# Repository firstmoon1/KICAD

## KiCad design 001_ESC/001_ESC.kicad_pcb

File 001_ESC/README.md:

THIS IS A DEMONSTRATION OF ESC(ELECTRONIC SPEED CONTROLLER) PROJECT,THAT WAS DONE BY MY INTEREST,GERBER AND PDF IS AVAILABLE.

PCB

3D FRONT OVERLAY

3D BACK OVERLAY

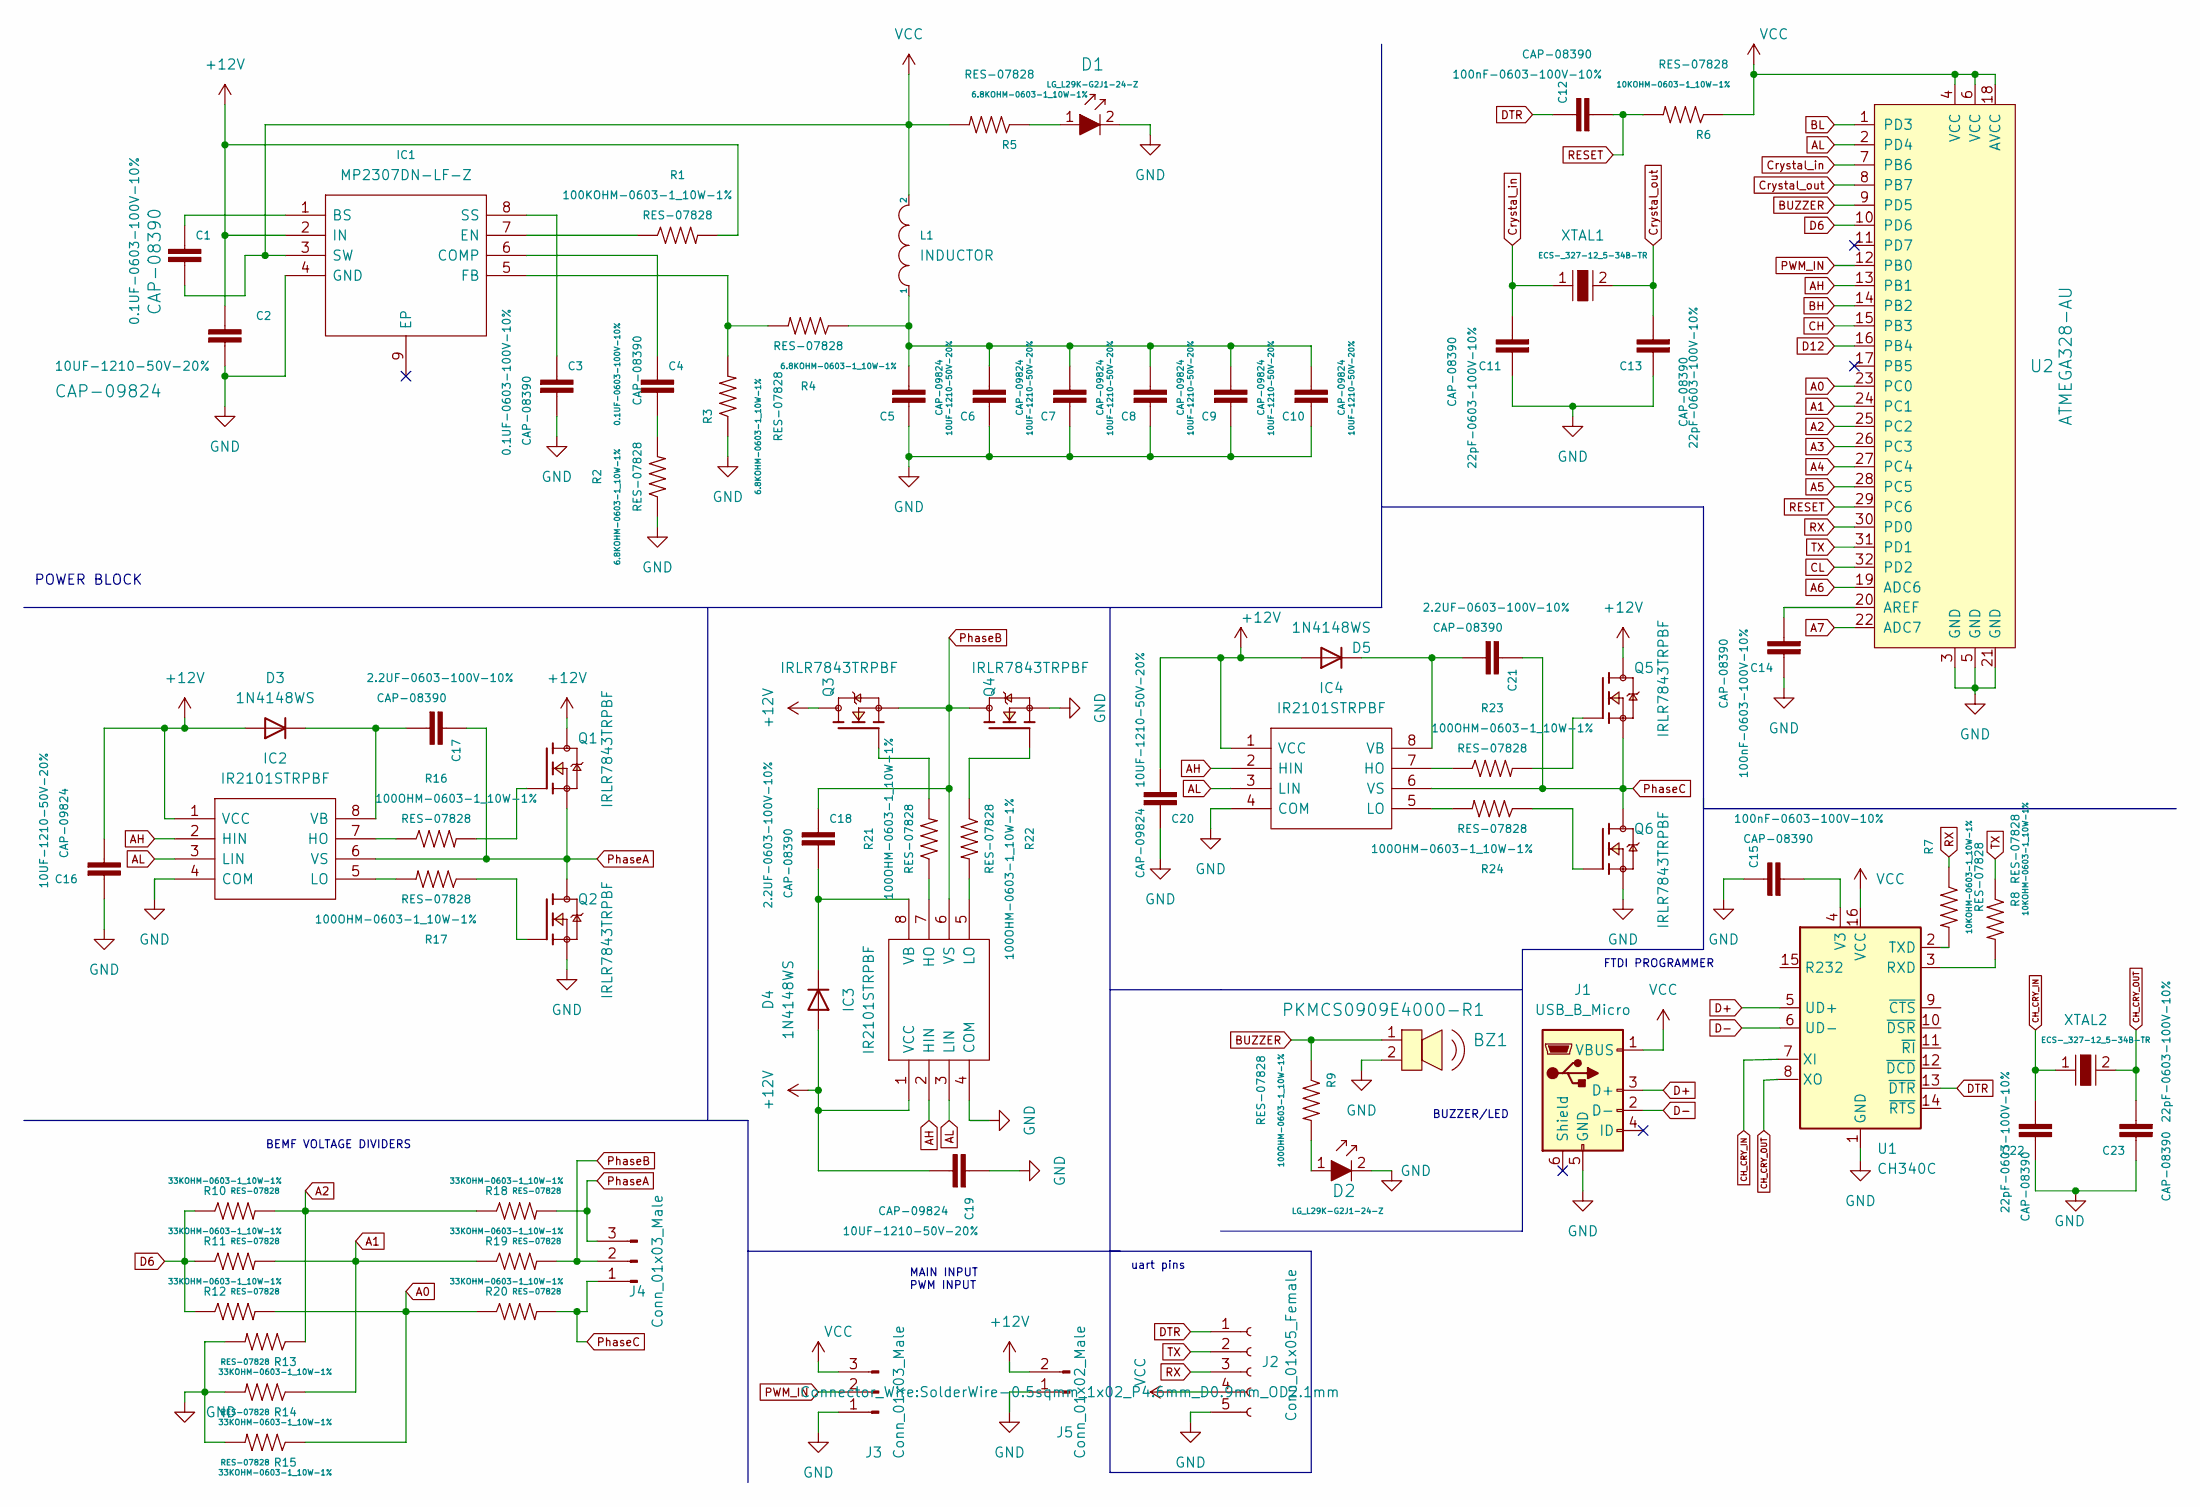
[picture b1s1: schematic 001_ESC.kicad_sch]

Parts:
BZ1: PKMCS0909E4000-R1; Buzzer_CUI_CPT-9019S-SMT; MPN PKMCS0909E4000-R1; Digi-Key_PN 490-9647-1-ND
C1, C3, C4: 0.1UF-0603-100V-10%; 0603
C2, C5, C6, C7, C8, C9, C10, C16, C19, C20: 10UF-1210-50V-20%; 1210
C11, C13, C22, C23: 22pF-0603-100V-10%; 0603
C12, C14, C15: 100nF-0603-100V-10%; 0603
C17, C18, C21: 2.2UF-0603-100V-10%; 0603
D1, D2: LG_L29K-G2J1-24-Z; 0603; MPN LG L29K-G2J1-24-Z; Digi-Key_PN 475-2709-1-ND
D3, D4, D5: 1N4148WS; D_SOD-323
IC1: MP2307DN-LF-Z; SOIC127P600X170-9N; Manufacturer_Part_Number MP2307DN-LF-Z; Mouser Part Number 946-MP2307DNLFZ
IC2, IC3, IC4: IR2101STRPBF; SOIC127P600X175-8N; Manufacturer_Part_Number IR2101STRPBF; Mouser Part Number 942-IR2101STRPBF
J1: USB_B_Micro; USB_Mini-B_Lumberg_2486_01_Horizontal
J2: Conn_01x05_Female; SolderWire-1.5sqmm_1x05_P6mm_D1.7mm_OD3mm
J3, J4: Conn_01x03_Male; SolderWire-0.5sqmm_1x03_P4.8mm_D0.9mm_OD2.3mm
J5: Conn_01x02_Male; SolderWire-0.5sqmm_1x02_P4.6mm_D0.9mm_OD2.1mm
L1: INDUCTOR; L_7.3x7.3_H4.5
Q1, Q2, Q3, Q4, Q5, Q6: IRLR7843TRPBF; TO229P990X239-3_4N; Digi-Key_Part_Number IRLR7843PBFTR-ND
R1: 100KOHM-0603-1_10W-1%; R_0201_0603Metric_Pad0.64x0.40mm_HandSolder
R2, R3, R4, R5: 6.8KOHM-0603-1_10W-1%; R_0201_0603Metric_Pad0.64x0.40mm_HandSolder
R6, R7, R8: 10KOHM-0603-1_10W-1%; R_0201_0603Metric_Pad0.64x0.40mm_HandSolder
R9, R16, R17, R21, R22, R23, R24: 100OHM-0603-1_10W-1%; R_0201_0603Metric_Pad0.64x0.40mm_HandSolder
R10, R11, R12, R13, R14, R15, R18, R19, R20: 33KOHM-0603-1_10W-1%; R_0201_0603Metric_Pad0.64x0.40mm_HandSolder
U1: CH340C; SOIC-16_3.9x9.9mm_P1.27mm
U2: ATMEGA328-AU; TQFP-32_7x7mm; MPN ATMEGA328-AU; Digi-Key_PN ATMEGA328-AU-ND
XTAL1, XTAL2: ECS-_327-12_5-34B-TR; SMD-2_3.2x1.5mm; MPN ECS-.327-12.5-34B-TR; Digi-Key_PN XC1617CT-ND

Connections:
+12V: C2.1, C16.1, C19.1, C20.1, D3.2 (A), D4.2 (A), D5.2 (A), IC1.2 (IN), IC2.1 (VCC), IC3.1 (VCC), IC4.1 (VCC), J5.2, Q1.4, Q3.4, Q5.4, R1.2
A0: R12.2, R15.1, R20.1, U2.23 (PC0)
A1: R11.2, R14.1, R19.1, U2.24 (PC1)
A2: R10.2, R13.1, R18.1, U2.25 (PC2)
A3: U2.26 (PC3)
A4: U2.27 (PC4)
A5: U2.28 (PC5)
A6: U2.19 (ADC6)
A7: U2.22 (ADC7)
AH: IC2.2 (HIN), IC3.2 (HIN), IC4.2 (HIN), U2.13 (PB1)
AL: IC2.3 (LIN), IC3.3 (LIN), IC4.3 (LIN), U2.2 (PD4)
BH: U2.14 (PB2)
BL: U2.1 (PD3)
BUZZER: BZ1.1, R9.1, U2.9 (PD5)
CH: U2.15 (PB3)
CH_CRY_IN: C22.2, U1.7 (XI), XTAL2.1
CH_CRY_OUT: C23.2, U1.8 (XO), XTAL2.2
CL: U2.32 (PD2)
Crystal_in: C11.2, U2.7 (PB6), XTAL1.1
Crystal_out: C13.2, U2.8 (PB7), XTAL1.2
D6: R10.1, R11.1, R12.1, U2.10 (PD6)
D12: U2.16 (PB4)
D+: J1.3 (D+), U1.5 (UD+)
D-: J1.2 (D-), U1.6 (UD-)
DTR: C12.1, J2.1, U1.13 (~DTR)
GND: BZ1.2, C2.2, C3.2, C5.2, C6.2, C7.2, C8.2, C9.2, C10.2, C11.1, C13.1, C14.1, C15.1, C16.2, C19.2, C20.2, C22.1, C23.1, D1.2, D2.2, IC1.4 (GND), IC2.4 (COM), IC3.4 (COM), IC4.4 (COM), J1.5 (GND), J2.5, J3.1, J5.1, Q2.3, Q4.3, Q6.3, R2.1, R3.1, R13.2, R14.2, R15.2, U1.1 (GND), U2.3 (GND), U2.5 (GND), U2.21 (GND)
unnamed: C1.1, IC1.1 (BS)
unnamed: C3.1, IC1.8 (SS)
unnamed: C4.1, IC1.6 (COMP)
unnamed: C4.2, R2.2
unnamed: C5.1, C6.1, C7.1, C8.1, C9.1, C10.1, L1.1, R4.1
unnamed: C14.2, U2.20 (AREF)
unnamed: C15.2, U1.4 (V3)
unnamed: C17.2, D3.1 (K), IC2.8 (VB)
unnamed: C18.2, D4.1 (K), IC3.8 (VB)
unnamed: C21.2, D5.1 (K), IC4.8 (VB)
unnamed: D1.1, R5.1
unnamed: D2.1, R9.2
unnamed: IC1.5 (FB), R3.2, R4.2
unnamed: IC1.7 (EN), R1.1
unnamed: IC2.5 (LO), R17.2
unnamed: IC2.7 (HO), R16.1
unnamed: IC3.5 (LO), R22.2
unnamed: IC3.7 (HO), R21.1
unnamed: IC4.5 (LO), R24.2
unnamed: IC4.7 (HO), R23.1
unnamed: Q1.1, R16.2
unnamed: Q2.1, R17.1
unnamed: Q3.1, R21.2
unnamed: Q4.1, R22.1
unnamed: Q5.1, R23.2
unnamed: Q6.1, R24.1
unnamed: R7.2, U1.2 (TXD)
unnamed: R8.2, U1.3 (RXD)
PWM_IN: J3.2, U2.12 (PB0)
PhaseA: C17.1, IC2.6 (VS), J4.3, Q1.3, Q2.4, R18.2
PhaseB: C18.1, IC3.6 (VS), J4.2, Q3.3, Q4.4, R19.2
PhaseC: C21.1, IC4.6 (VS), J4.1, Q5.3, Q6.4, R20.2
RESET: C12.2, R6.2, U2.29 (PC6)
RX: J2.3, R7.1, U2.30 (PD0)
TX: J2.2, R8.1, U2.31 (PD1)
VCC: C1.2, IC1.3 (SW), J1.1 (VBUS), J2.4, J3.3, L1.2, R5.2, R6.1, U1.16 (VCC), U2.4 (VCC), U2.6 (VCC), U2.18 (AVCC)

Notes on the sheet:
POWER BLOCK
uart pins
BUZZER/LED
BEMF VOLTAGE DIVIDERS
MAIN INPUT PWM INPUT
FTDI PROGRAMMER

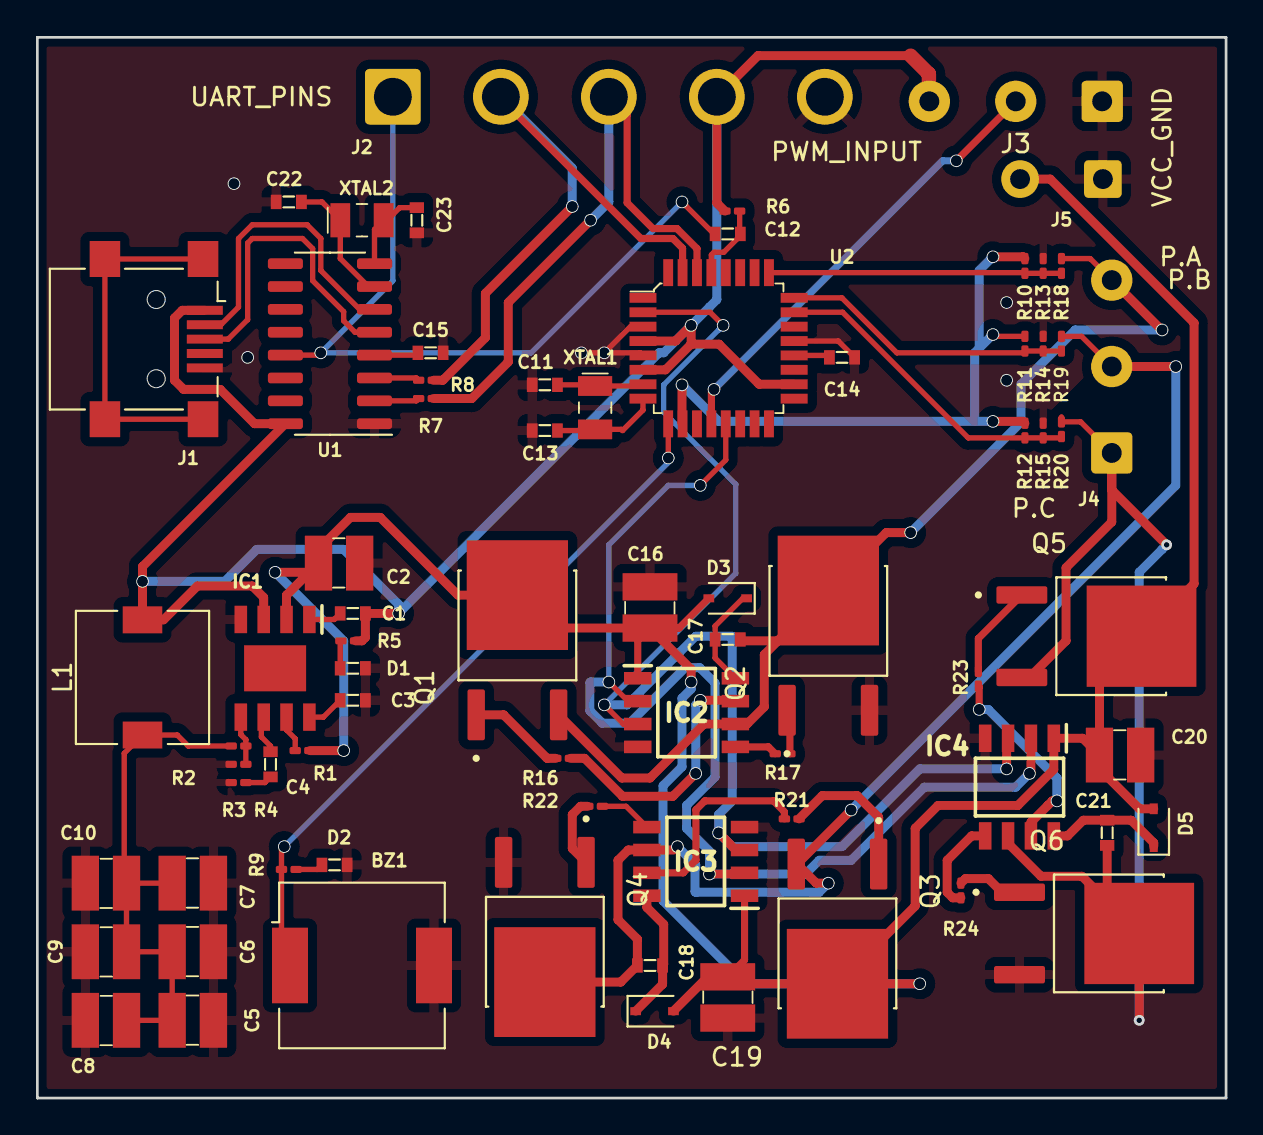
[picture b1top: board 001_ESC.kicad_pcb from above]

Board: 2 copper layers, 66.0 x 58.9 mm, 73 parts (0 on the bottom side), 52 nets.

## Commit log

2023-01-31 project1
2023-01-31 update.
2023-01-31 .
    .
